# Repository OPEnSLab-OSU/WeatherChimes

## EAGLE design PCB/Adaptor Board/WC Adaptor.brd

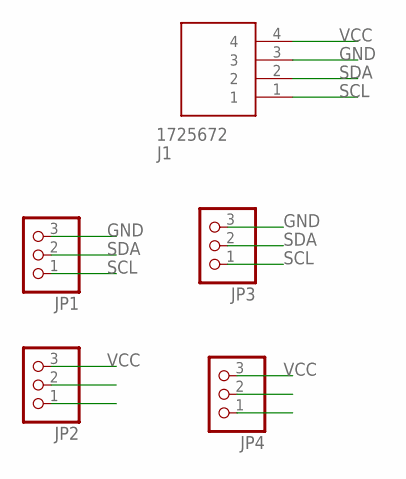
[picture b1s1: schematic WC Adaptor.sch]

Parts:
J1: 1725672
JP1, JP2, JP3, JP4: PINHD-1X3; 1X03

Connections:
GND: J1.3, JP1.3, JP3.3
SCL: J1.1, JP1.1, JP3.1
SDA: J1.2, JP1.2, JP3.2
VCC: J1.4, JP2.3, JP4.3

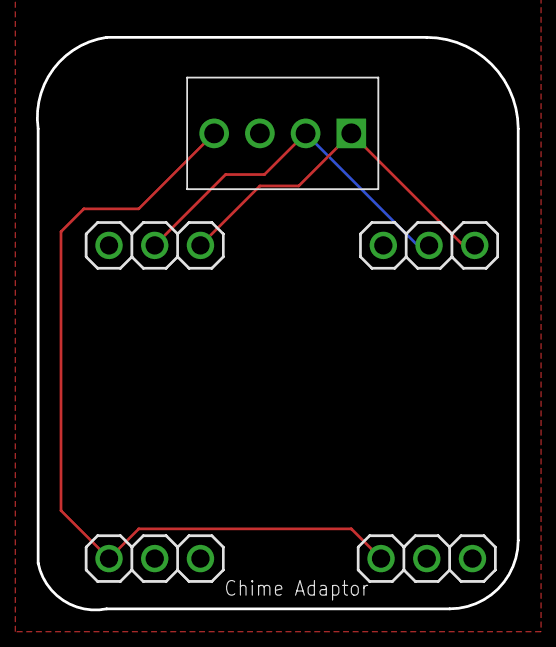
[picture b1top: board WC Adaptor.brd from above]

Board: 2 copper layers, 26.7 x 31.8 mm, 5 parts (0 on the bottom side), 4 nets.

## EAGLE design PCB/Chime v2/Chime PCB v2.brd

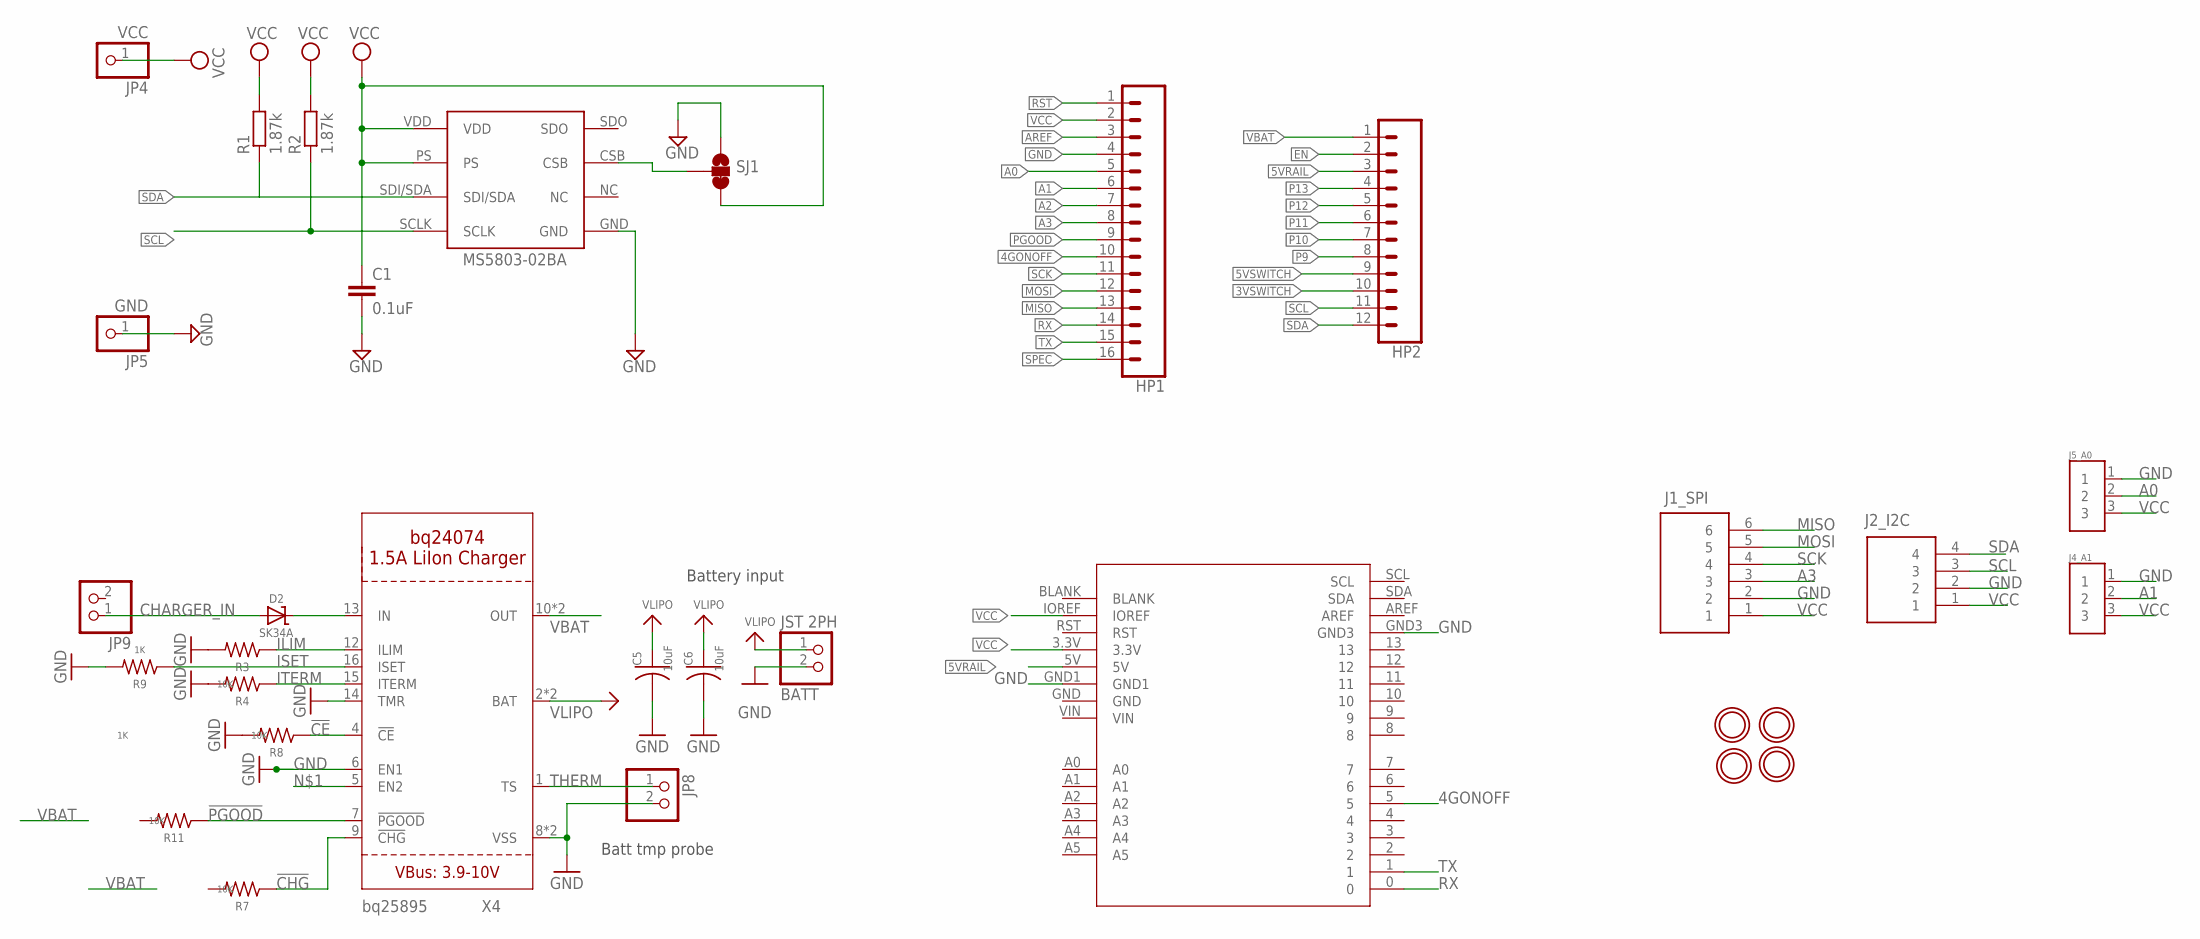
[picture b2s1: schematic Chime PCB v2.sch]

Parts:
BATT: JST 2PH; JST-PH-2-SMT-RA
C1: 0.1uF; C0805
C5, C6: 10uF; C0805K
D2: SK34A; SMADIODE
HP1: CONN_16; 1X16
HP2: CONN_12; 1X12
J1_SPI: 1725698
J2_I2C: 1725672
J4_A1, J5_A0: 282834-3; TE_282834-3
JP4: VCC; 1X01
JP5: GND; 1X01
JP8, JP9: PINHD-1X2; 1X02
R1, R2: 1.87k; R0805
R3, R9: 1K; M0805
R4, R7, R8, R11: 10K; M0805
SJ1: JUMPER-SMT_3_1-NC_TRACE_SILK; SMT-JUMPER_3_1-NC_TRACE_SILK
U1: MS5803-02BA
U$1: LTE_BOARD; LTE_BOARD_FOOTPRINT
U$2, U$3, U$4, U$5: MOUNTINGHOLE2.5; MOUNTINGHOLE_2.5_PLATED
X4: BQ24074; QFN16_3MM

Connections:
3VSWITCH: HP2.10
4GONOFF: HP1.10, U$1.5
5VRAIL: HP2.3, U$1.5V
5VSWITCH: HP2.9
!CE: R8.1, X4.4 (!CE)
!CHG: R7.1, X4.9 (!CHG)
!PGOOD: R11.1, X4.7 (!PGOOD)
A0: HP1.5, J5_A0.2
A1: HP1.6, J4_A1.2
A2: HP1.7
A3: HP1.8, J1_SPI.3
AREF: HP1.3
CHARGER_IN: D2.A, JP9.1
EN: HP2.2
GND: BATT.2 (1), C1.2, C5.2, C6.2, HP1.4, J1_SPI.2, J2_I2C.2, J4_A1.1, J5_A0.1, JP5.1, JP8.2, R3.2, R4.2, R8.2, R9.2, SJ1.1, U1.GND, U$1.GND1, U$1.GND3, X4.6 (EN1), X4.8 (VSS), X4.14 (TMR), X4.THERMAL (VSS)
ILIM: R3.1, X4.12 (ILIM)
ISET: R9.1, X4.16 (ISET)
ITERM: R4.1, X4.15 (ITERM)
MISO: HP1.13, J1_SPI.6
MOSI: HP1.12, J1_SPI.5
unnamed: D2.C, X4.13 (IN)
unnamed: SJ1.2, U1.CSB
P9: HP2.8
P10: HP2.7
P11: HP2.6
P12: HP2.5
P13: HP2.4
PGOOD: HP1.9
RST: HP1.1
RX: HP1.14, U$1.0
SCK: HP1.11, J1_SPI.4
SCL: HP2.11, J2_I2C.3, R2.1, U1.SCLK
SDA: HP2.12, J2_I2C.4, R1.1, U1.SDI/SDA
SPEC: HP1.16
THERM: JP8.1, X4.1 (TS)
TX: HP1.15, U$1.1
VBAT: HP2.1, X4.10 (OUT), X4.11 (OUT)
VCC: C1.1, HP1.2, J1_SPI.1, J2_I2C.1, J4_A1.3, J5_A0.3, JP4.1, R1.2, R2.2, SJ1.3, U1.PS, U1.VDD, U$1.3.3V, U$1.IOREF
VLIPO: BATT.1 (2), C5.1, C6.1, X4.2 (BAT), X4.3 (BAT)

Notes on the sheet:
Batt tmp probe
Battery input

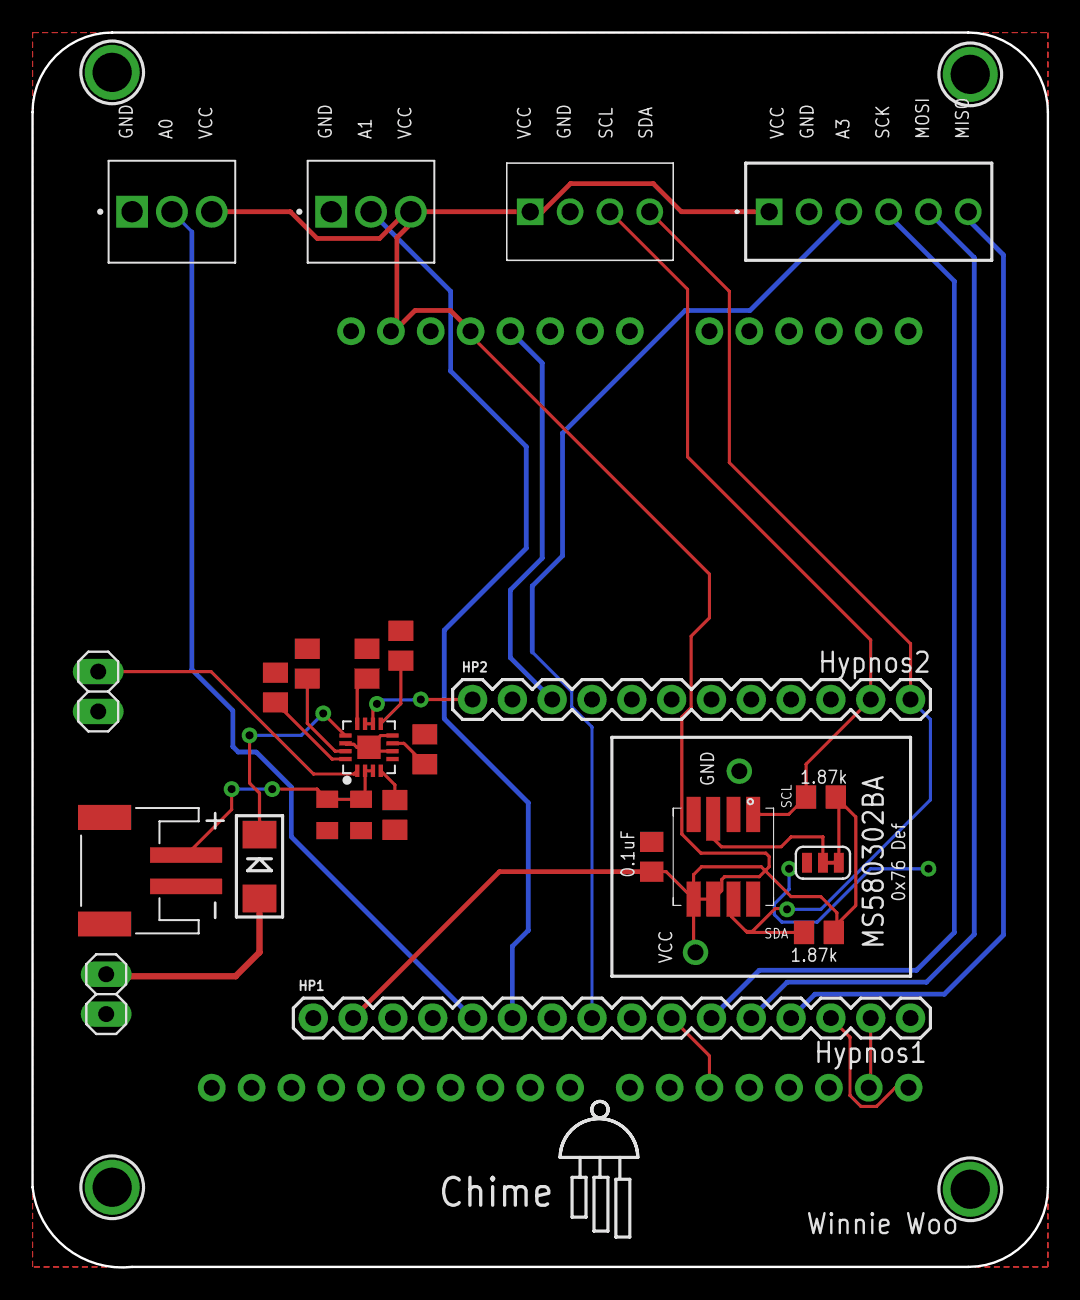
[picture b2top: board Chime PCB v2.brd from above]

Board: 2 copper layers, 64.8 x 78.8 mm, 31 parts (1 on the bottom side), 26 nets.

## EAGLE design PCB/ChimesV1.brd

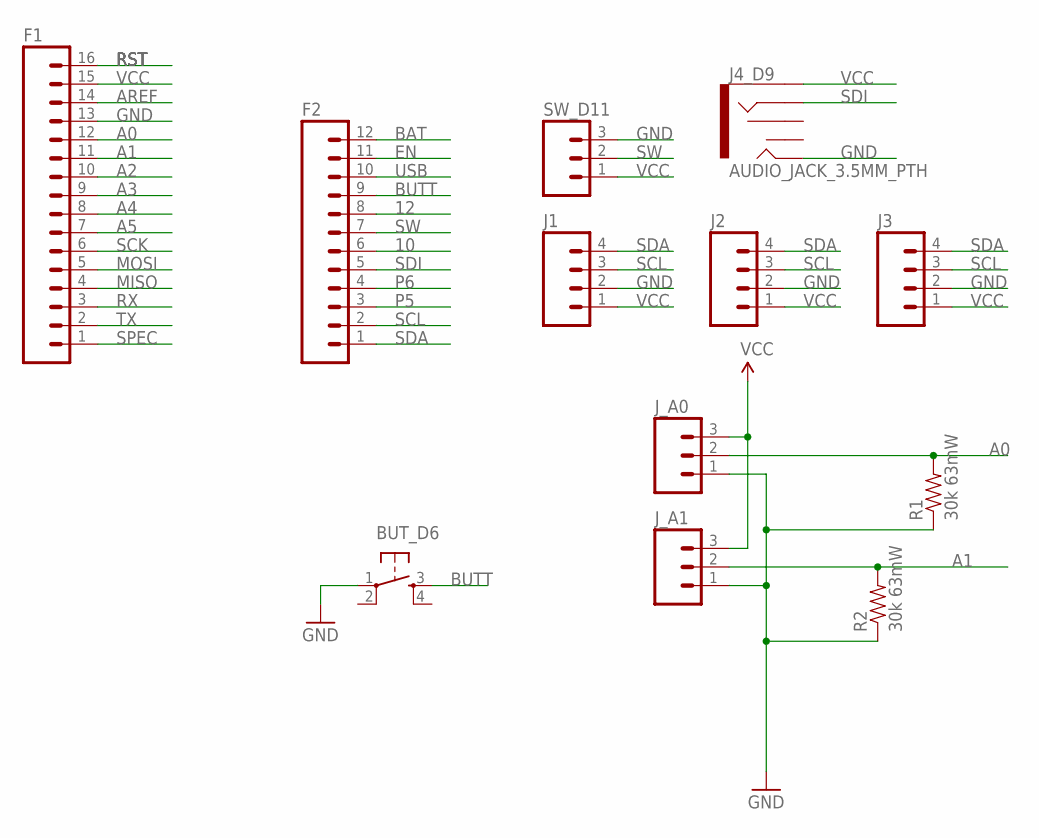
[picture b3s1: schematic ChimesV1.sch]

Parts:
BUT_D6: TAC_SWITCHPTH; TACTILE-PTH
F1: M16PTH; 1X16
F2: M12PTH; 1X12
J1, J2, J3: M04PTH; 1X04
J4_D9: AUDIO_JACK_3.5MM_PTH; AUDIO-JACK
J_A0, J_A1: M03JST-PTH-VERT; JST-3-PTH-VERT
R1, R2: 30k 63mW; 1206
SW_D11: M03PTH; 1X03

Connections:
10: F2.6
12: F2.8
A0: F1.12, J_A0.2, R1.2
A1: F1.11, J_A1.2, R2.2
A2: F1.10
A3: F1.9
A4: F1.8
A5: F1.7
AREF: F1.14
BAT: F2.12
BUTT: BUT_D6.3, F2.9
EN: F2.11
GND: BUT_D6.1, F1.13, J1.2, J2.2, J3.2, J4_D9.TIP, J_A0.1, J_A1.1, R1.1, R2.1, SW_D11.3
MISO: F1.4
MOSI: F1.5
P5: F2.3
P6: F2.4
RST: F1.16
RX: F1.3
SCK: F1.6
SCL: F2.2, J1.3, J2.3, J3.3
SDA: F2.1, J1.4, J2.4, J3.4
SDI: F2.5, J4_D9.RING
SPEC: F1.1
SW: F2.7, SW_D11.2
TX: F1.2
USB: F2.10
VCC: F1.15, J1.1, J2.1, J3.1, J4_D9.SLEEVE, J_A0.3, J_A1.3, SW_D11.1

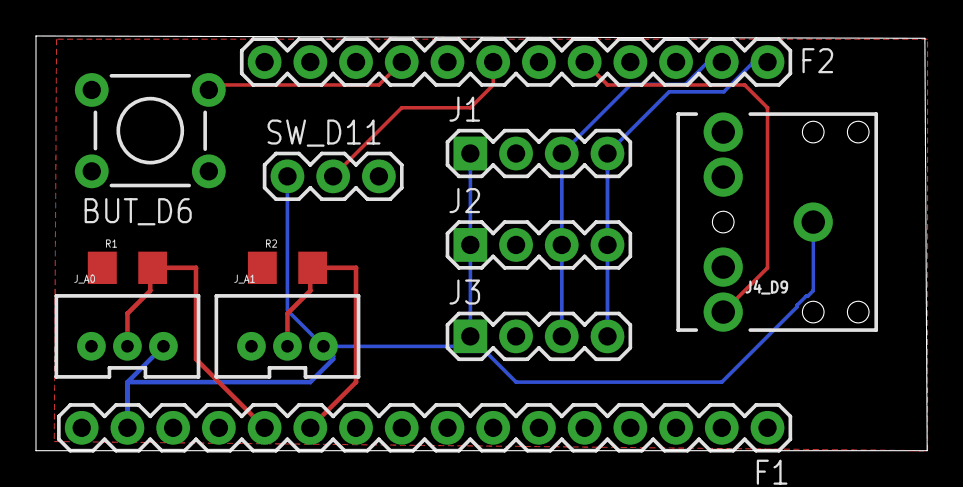
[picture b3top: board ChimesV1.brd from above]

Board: 2 copper layers, 49.5 x 23.0 mm, 12 parts (0 on the bottom side), 9 nets.

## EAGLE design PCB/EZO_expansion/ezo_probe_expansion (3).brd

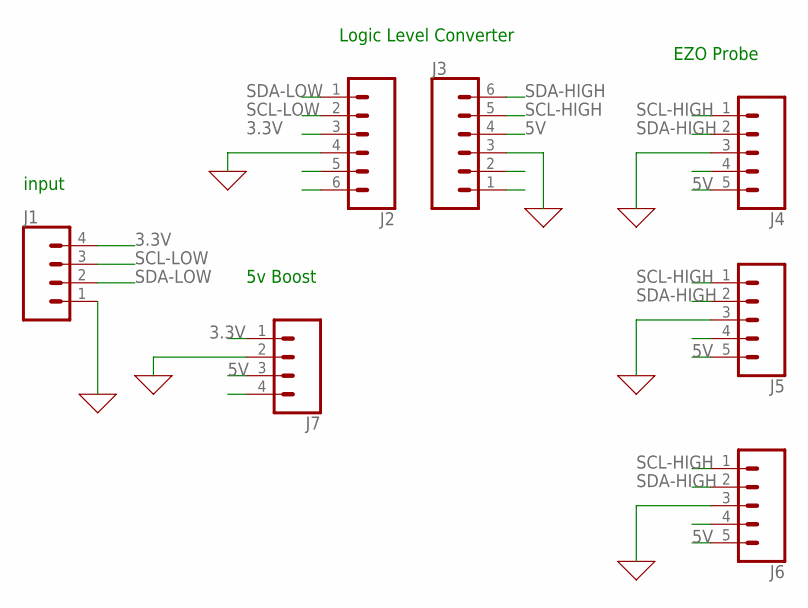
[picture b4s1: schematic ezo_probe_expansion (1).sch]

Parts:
J1, J7: CONN_04PTH; 1X04
J2, J3: CONN_06SILK_FEMALE_PTH; 1X06
J4, J5, J6: CONN_05PTH; 1X05

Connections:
3.3V: J1.4, J2.3, J7.1
5V: J3.4, J4.5, J5.5, J6.5, J7.3
GND: J1.1, J2.4, J3.3, J4.3, J5.3, J6.3, J7.2
SCL-HIGH: J3.5, J4.1, J5.1, J6.1
SCL-LOW: J1.3, J2.2
SDA-HIGH: J3.6, J4.2, J5.2, J6.2
SDA-LOW: J1.2, J2.1

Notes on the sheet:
input
5v Boost
Logic Level Converter
EZO Probe

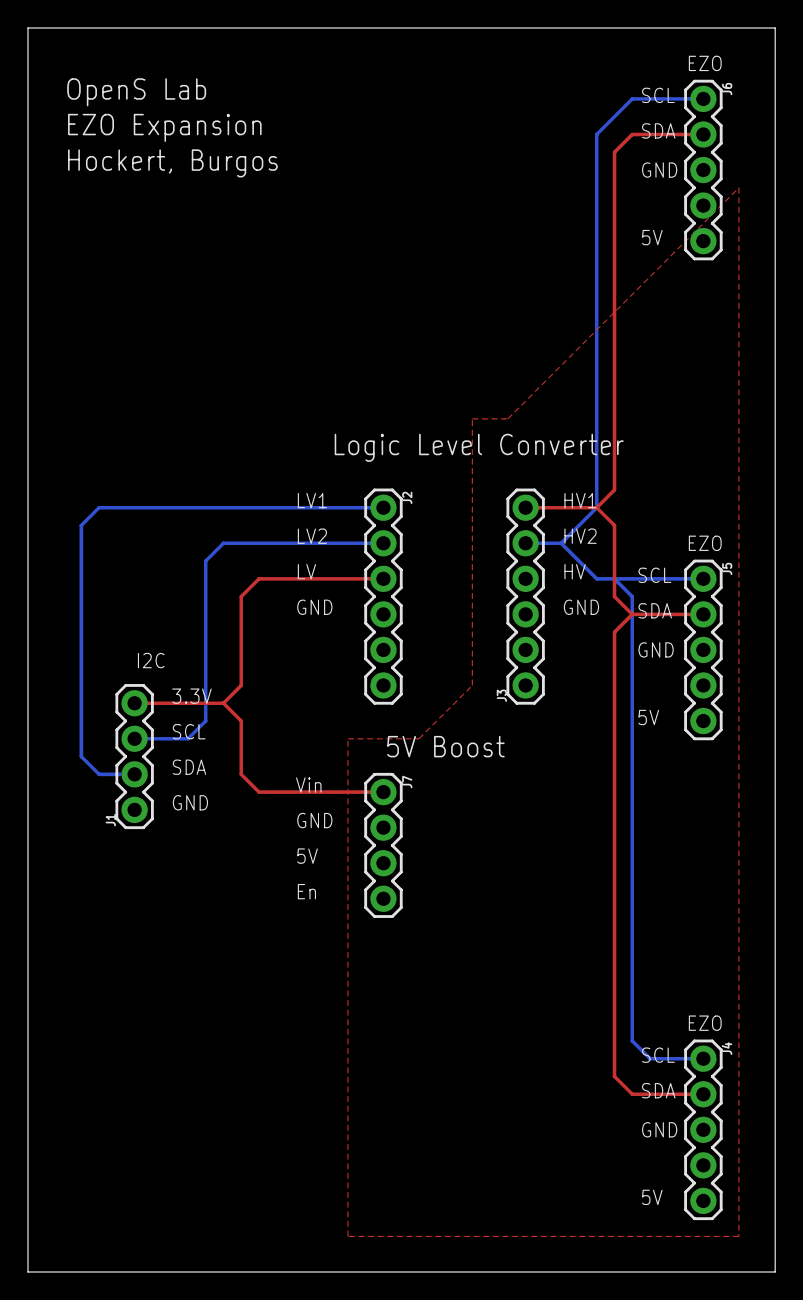
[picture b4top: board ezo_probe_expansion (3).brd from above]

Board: 2 copper layers, 53.4 x 88.9 mm, 7 parts (0 on the bottom side), 7 nets.

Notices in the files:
parts and their libraries:
microbuilder: This work is placed in the public domain, and may be freely used for commercial and non-commercial work with the following conditions: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
SparkFun-Connectors: Licensing: Creative Commons ShareAlike 4.0 International - https://creativecommons.org/licenses/by-sa/4.0
